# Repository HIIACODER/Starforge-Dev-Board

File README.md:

# Starforge-Dev-Board
A simple 4 layer RP2040 Dev Board powered by USB-C, with data and power delivery. Uses 24 GPIO and 4 ADC pins, alongside 1 3.3V and one 5V output. There is also 7 ground pins with 2 debug pins. It also has a red signal LED for any use case, utilizing the single unused standard GPIO pin.

My goal with this project was to learn how to route properly and effectively on a PCB including how to manage decoupling caps and general power routing because that is what I struggle with. I also wanted a simple board to use for my projects.

This project should:
- help me develop a base to apply to future projects
- be a simple dev board I can use for other projects

## PCB
Here is my PCB! This PCB was designed in KiCAD.

### General PCB design images

Schematic:

Top View (3d render):

Bottom View (3d render):

PCB Design:

First Layer: 

Second Layer:

Third Layer: 

Fourth Layer: 

### Layer Stackup
The board contains 4 layers. The purpose of all layers listed below.

| Layer | Description |
| :--- | :--- |
| 1 | Main routing layer |
| 2 | First ground layer for reference and signal separation |
| 3 | Second ground layer for reference and signal separation |
| 4 | Overflow routing layer |
### Flashing Instructions
Here are steps to flash a file to the MCU! 
1. Hold down the BOOTSEL button (the only button on the board) while plugging the board into your computer via USBC
2. The board will show up as a USB mass storage device
3. Compile your .uf2 binary file through external methods (C/C++ SDK, MicroPython, CircuitPython, etc)
4. Drag your compiled .uf2 file onto the drive. The board should automatically reboot and run the newly uploaded firmware!

## BOM

All SMD parts utilize 0402 passives to minimize board surface area. JLCPCB / LCSC part numbers are included below for reference.

| Item | Component / Description | Qty | Designators | Footprint | JLCPCB Part # | Unit Price (USD) |
| :--- | :--- | :---: | :--- | :--- | :--- | :--- |
| 1 | RP2040 Microcontroller | 1 | `U1` | `QFN-56_L7.0-W7.0-P0.4` | `C2040` | $0.70 |
| 2 | P25Q16SH-UXH-IR (16Mbit Flash) | 1 | `U3` | `USON8_L3.0-W2.0-P0.5` | `C7466821` | $0.15 |
| 3 | MCP1700T-3302E/TT (3.3V LDO) | 1 | `U2` | `SOT-23` | `C39051` | $0.44 |
| 4 | HC-TYPE-C-16P-01A (USB-C) | 1 | `J1` | `USB_C_Receptacle_16P` | `C2894897` | $0.25 |
| 5 | Crystal_GND24 (12MHz Crystal) | 1 | `Y1` | `SMD_4P-L3.2-W2.5` | `C9002` | $0.09 |
| 6 | TS-1088 Tactile Switch | 1 | `SW1` | `SW-SMD_L3.9-W3.0-P4.45` | `C720477` | $0.05 |
| 7 | Header Male 2.54mm 1x20 | 2 | `J2, J3` | `PinHeader_1x20_P2.54mm` | `C50981` | $0.10 |
| 8 | Header Male 2.54mm 1x3 | 1 | `H1` | `HDR-TH_3P-P2.54mm` | `C2937625` | $0.03 |
| 9 | 100nF Capacitor | 11 | `C2-C9, C11, C12, C17` | `C_0402` | `C1525` | $0.002 |
| 10 | 1uF Capacitor | 2 | `C1, C10` | `C_0402` | `C29266` | $0.003 |
| 11 | 10uF Capacitor | 2 | `C13, C14` | `C_0402` | `C15525` | $0.015 |
| 12 | 33pF Load Capacitor | 2 | `C15, C16` | `C_0402` | `C107005` | $0.002 |
| 13 | 5.1k Resistor | 2 | `R1, R2` | `R_0402` | `C25905` | $0.001 |
| 14 | 27Ω Resistor | 2 | `R5, R6` | `R_0402` | `C2909343` | $0.001 |
| 15 | 1k Resistor | 2 | `R4, R7` | `R_0402` | `C11702` | $0.001 |
| 16 | 10k Resistor | 1 | `R3` | `R_0402` | `C25744` | $0.001 |
| 17 | Tuozhan Red LED (1.91V) | 1 | `D1` | `LED_0603` | `C7496820` | $0.003 |
| 18 | 150Ω Resistor | 1 | `R8` | `R_0402` | `C25082` | $0.001 |
### Prices on JLCPCB:
NOTE: THESE PRICES DO NOT CONTAIN TAXES

PCB (5x): $2.0

PCBA (2x): $48.17

Shipping on Global Standard Direct Line: $3.30

Thanks for viewing this project!

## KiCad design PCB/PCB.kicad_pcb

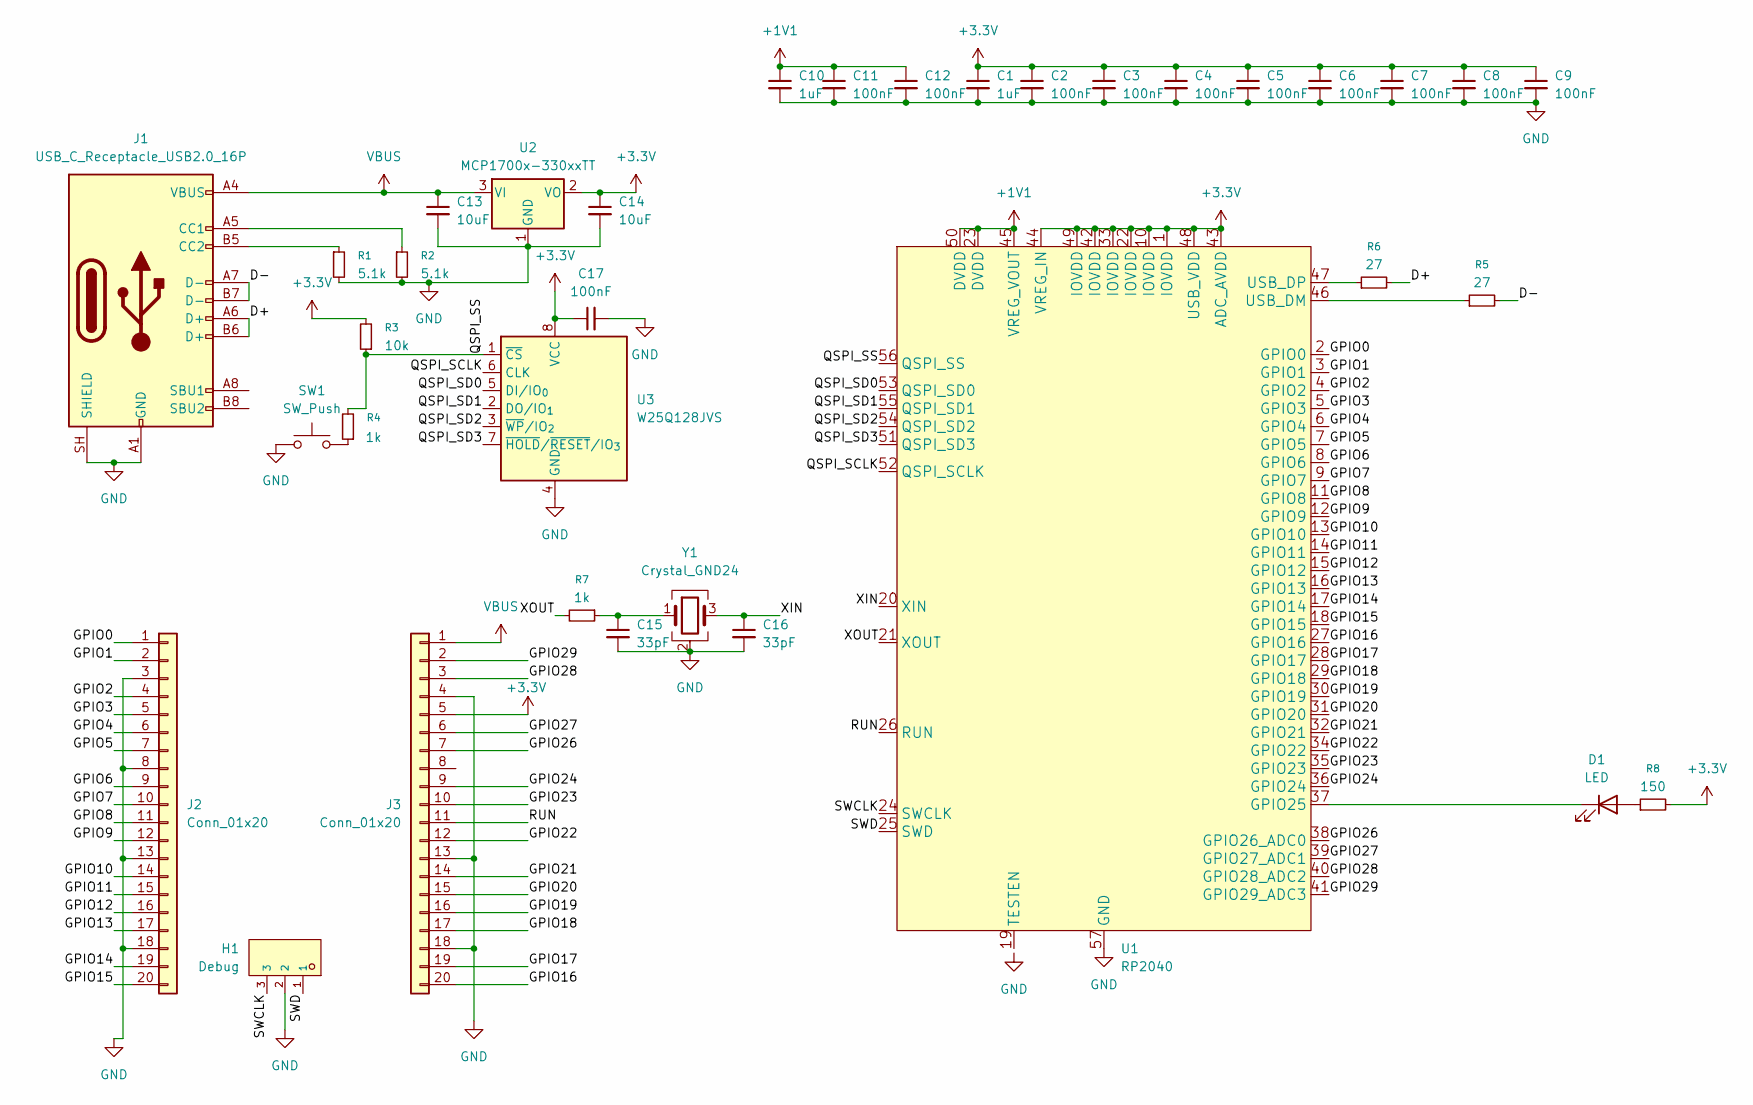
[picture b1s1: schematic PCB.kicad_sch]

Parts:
C1, C10: 1uF; C_0402_1005Metric
C2, C3, C4, C5, C6, C7, C8, C9, C11, C12, C17: 100nF; C_0402_1005Metric
C13, C14: 10uF; C_0402_1005Metric
C15, C16: 33pF; C_0402_1005Metric
D1: LED; C7496820_LED0603-RD
H1: Debug; C2937625_HDR-TH_3P-P2_54-V-M_PZ254V-11-03P; LCSC C2937625
J1: USB_C_Receptacle_USB2.0_16P; USB_C_Receptacle_HCTL_HC-TYPE-C-16P-01A
J2, J3: Conn_01x20; C50981_HDR-TH_20P-P2_54-V-M-1
R1, R2: 5.1k; R_0402
R3: 10k; R_0402
R4, R7: 1k; R_0402
R5, R6: 27; R_0402
R8: 150; R_0402
SW1: SW_Push; C720477_SW-SMD_L3_9-W3_0-P4_45
U1: RP2040; C2040_LQFN-56_L7_0-W7_0-P0_4-EP; LCSC C2040
U2: MCP1700x-330xxTT; SOT-23
U3: W25Q128JVS; C7466821_USON8_L3_0-W2_0-P0_50-BL-EP
Y1: Crystal_GND24; C9002_CRYSTAL-SMD_4P-L3_2-W2_5-BL

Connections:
+1V1: C10.1, C11.1, C12.1, U1.23 (DVDD), U1.45 (VREG_VOUT), U1.50 (DVDD)
+3.3V: C1.1, C2.1, C3.1, C4.1, C5.1, C6.1, C7.1, C8.1, C9.1, C14.1, C17.1, J3.5, R3.2, R8.2, U1.1 (IOVDD), U1.10 (IOVDD), U1.22 (IOVDD), U1.33 (IOVDD), U1.42 (IOVDD), U1.43 (ADC_AVDD), U1.44 (VREG_IN), U1.48 (USB_VDD), U1.49 (IOVDD), U2.2 (VO), U3.8 (VCC)
/D+: J1.A6 (D+), J1.B6 (D+), R6.2
/D-: J1.A7 (D-), J1.B7 (D-), R5.2
/GPIO0: J2.1, U1.2 (GPIO0)
/GPIO1: J2.2, U1.3 (GPIO1)
/GPIO2: J2.4, U1.4 (GPIO2)
/GPIO3: J2.5, U1.5 (GPIO3)
/GPIO4: J2.6, U1.6 (GPIO4)
/GPIO5: J2.7, U1.7 (GPIO5)
/GPIO6: J2.9, U1.8 (GPIO6)
/GPIO7: J2.10, U1.9 (GPIO7)
/GPIO8: J2.11, U1.11 (GPIO8)
/GPIO9: J2.12, U1.12 (GPIO9)
/GPIO10: J2.14, U1.13 (GPIO10)
/GPIO11: J2.15, U1.14 (GPIO11)
/GPIO12: J2.16, U1.15 (GPIO12)
/GPIO13: J2.17, U1.16 (GPIO13)
/GPIO14: J2.19, U1.17 (GPIO14)
/GPIO15: J2.20, U1.18 (GPIO15)
/GPIO16: J3.20, U1.27 (GPIO16)
/GPIO17: J3.19, U1.28 (GPIO17)
/GPIO18: J3.17, U1.29 (GPIO18)
/GPIO19: J3.16, U1.30 (GPIO19)
/GPIO20: J3.15, U1.31 (GPIO20)
/GPIO21: J3.14, U1.32 (GPIO21)
/GPIO22: J3.12, U1.34 (GPIO22)
/GPIO23: J3.10, U1.35 (GPIO23)
/GPIO24: J3.9, U1.36 (GPIO24)
/GPIO26: J3.7, U1.38 (GPIO26_ADC0)
/GPIO27: J3.6, U1.39 (GPIO27_ADC1)
/GPIO28: J3.3, U1.40 (GPIO28_ADC2)
/GPIO29: J3.2, U1.41 (GPIO29_ADC3)
/QSPI_SCLK: U1.52 (QSPI_SCLK), U3.6 (CLK)
/QSPI_SD0: U1.53 (QSPI_SD0), U3.5 (DI/IO_{0})
/QSPI_SD1: U1.55 (QSPI_SD1), U3.2 (DO/IO_{1})
/QSPI_SD2: U1.54 (QSPI_SD2), U3.3 (~WP/IO_{2})
/QSPI_SD3: U1.51 (QSPI_SD3), U3.7 (~HOLD/~RESET/IO_{3})
/QSPI_SS: R3.1, R4.2, U1.56 (QSPI_SS), U3.1 (~CS)
/RUN: J3.11, U1.26 (RUN)
/SWCLK: H1.3, U1.24 (SWCLK)
/SWD: H1.1, U1.25 (SWD)
/XIN: C16.1, U1.20 (XIN), Y1.3
/XOUT: R7.2, U1.21 (XOUT)
GND: C1.2, C2.2, C3.2, C4.2, C5.2, C6.2, C7.2, C8.2, C9.2, C10.2, C11.2, C12.2, C13.2, C14.2, C15.2, C16.2, C17.2, H1.2, J1.A1 (GND), J1.A12 (GND), J1.B1 (GND), J1.B12 (GND), J1.SH (SHIELD), J2.3, J2.8, J2.13, J2.18, J3.4, J3.13, J3.18, R1.2, R2.2, SW1.1, U1.57 (GND), U2.1 (GND), U3.4 (GND), Y1.2 (G), Y1.4 (G)
unnamed: C15.1, R7.1, Y1.1
unnamed: D1.2 (A), R8.1
unnamed: D1.1 (K), U1.37 (GPIO25)
unnamed: J1.A5 (CC1), R2.1
unnamed: J1.B5 (CC2), R1.1
unnamed: R4.1, SW1.2
unnamed: R5.1, U1.46 (USB_DM)
unnamed: R6.1, U1.47 (USB_DP)
VBUS: C13.1, J1.A4 (VBUS), J1.A9 (VBUS), J1.B4 (VBUS), J1.B9 (VBUS), J3.1, U2.3 (VI)

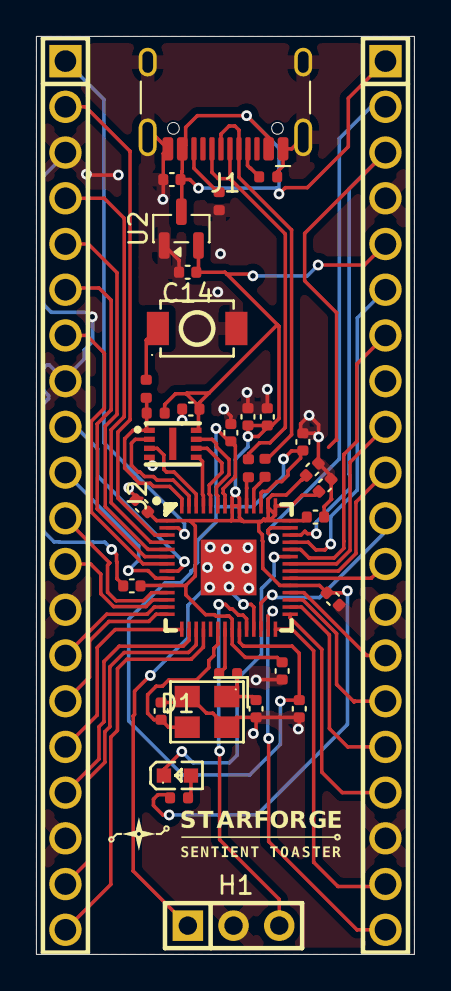
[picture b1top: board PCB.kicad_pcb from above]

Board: 4 copper layers, 21.0 x 51.0 mm, 35 parts (0 on the bottom side), 54 nets.

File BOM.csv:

Comment,Designator,Footprint,JLCPCB Part #（optional）
1uF,"C1,C10",C_0402_1005Metric,C29266
100nF,"C2,C3,C4,C5,C6,C7,C8,C9,C11,C12,C17",C_0402_1005Metric,C1525
10uF,"C13,C14",C_0402_1005Metric,C15525
33pF,"C15,C16",C_0402_1005Metric,C107005
Header-Male-2.54_1x3,H1,C2937625_HDR-TH_3P-P2_54-V-M_PZ254V-11-03P,C2937625
HC-TYPE-C-16P-01A,J1,USB_C_Receptacle_HCTL_HC-TYPE-C-16P-01A,C2894897
Header-Male-2.54_1x20,"J2,J3",PinHeader_1x20_P2.54mm_Vertical,C50981
5.1K,"R1,R2",R_0402,C25905
10K,R3,R_0402,C25744
1K,"R4,R7",R_0402,C11702
27R,"R5,R6",R_0402,C2909343
TS-1088-AR02016,SW1,C720477_SW-SMD_L3_9-W3_0-P4_45,C720477
RP2040,U1,C2040_LQFN-56_L7_0-W7_0-P0_4-EP,C2040
MCP1700T-3302E/TT,U2,SOT-23,C39051
P25Q16SH-UXH-IR,U3,lcsc_footprints:C7466821_USON8_L3_0-W2_0-W2_0-P0_50-BL-EP,C7466821
Crystal_GND24,Y1,C9002_CRYSTAL-SMD_4P-L3_2-W2_5-BL,C9002
